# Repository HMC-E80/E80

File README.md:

# E80

This repository includes Arduino sketches (.ino) for the Teensy on the E80 motherboard.
The files for each lab are included in a separate folder.
The .ino files in each lab folder share the same name as the folder (e.g., `E80_Lab_01.ino` is in a folder named `E80_Lab_01.ino`).
This is a requirement for the Arduino IDE.

This respository also includes a [folder](./libraries/) of all the libraries you need for the various hardware peripherals on your motherboard (e.g., the GPS, and intertial measurement unit (IMU)).

The [MATLAB](./MATLAB/) folder contains the various MATLAB `.m` files which are used throughout the labs.

# How to Use this Repository

## Git Setup
You will need to configure Git on your machine.
Git is a distributed version control system.
This means you can download a local clone of a collection of source code files and easily track the changes that you make to your code.
While we won't be using all the features of git in E80, we will introduce you to the main features that will enable you to interact with the code base for your robot.

First, you need to install Git on your computer.
We recommend that for this class you use [Git Desktop](https://desktop.github.com) which provides a convenient GUI interface for interacting with the code.

1. Download and install the latest version of Git Desktop [here](https://desktop.github.com).
2. Navigate to the [E80 GitHub repository](https://github.com/HMC-E80/E80) and click `Code > Open with GitHub Desktop`. You will get a prompt to clone/download the repo, and GitHub Desktop will ask you where to save the files. Choose a location on your hard drive where you want to save the files (i.e., NOT in a folder that is synchronized in the cloud like a Google Drive File Stream folder). You should choose a location on your hard drive to minimize the chances of having any data corrupted.
   - NOTE: If for some reason clicking `Open with GitHub Desktop` is not working properly, simply copy the URL for the repository (e.g., `https://github.com/HMC-E80/E80`) and then manually clone the repository in GitHub Desktop using `File > Clone Repository`. Enter the copied URL into the "Respository URL" field.

## Arduino IDE Setup
Follow the instructions below to download and use this code within the Arduino IDE.
1. If you have not yet installed the Arduino IDE, install it from [here](https://www.arduino.cc/en/software). The version as of this writing is 2.0.3 but higher version numbers should also work fine.
2. Follow the instructions [here](https://www.pjrc.com/arduino-ide-2-0-0-teensy-support/) to configure support for the Teensy board within the Arduino IDE.
3. After downloading the code, open the Arduino IDE and go to __Arduino IDE > Settings__ if you are using a MAC and __file > preferences__ if you are using Windows. Change the Sketchbook location to point to the folder you downloaded from GitHub.

4. Now you if you click on the Sketchbook icon in the toolbar on the left side of the Arduino IDE you should see all the code for your E80 motherboard listed and available. Open up the `E80_Lab_01.ino` sketch and Verify it to check that it compiles and all the libraries are properly downloaded.

Congratulations, you are now set up and have the default E80 source code downloaded!
If you have any issues with these instructions, please reach out to one of the instructors.

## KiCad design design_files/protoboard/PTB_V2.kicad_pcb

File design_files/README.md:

# E80 Hardware Design Files

This directory contains the hardware design files for the E80 robot platform, including PCB schematics, layouts, and gerber files.

## Directory Structure

- **adapter_board/** - Design files for the Teensy 4.0 to 3.2 adapter board
  - KiCad project files and custom component libraries

- **motherboard/** - Design files for the main E80 Motherboard (MTB)
  - Schematics, PCB layouts, and documentation
  - Contains MTB_V3.0.2021 with complete KiCad project files

- **protoboard/** - Design files for the prototyping board (PTB)
  - Includes KiCad project files and gerber files for manufacturing

## Usage

These design files are provided for reference and can be viewed or modified using KiCad 5.0 or later. The gerber files in the PTB_V2_Gerbers directory can be sent directly to PCB manufacturers for reproduction.

## Documentation

Schematic PDFs are provided for the motherboard in the motherboard directory for easy reference without needing to open KiCad.

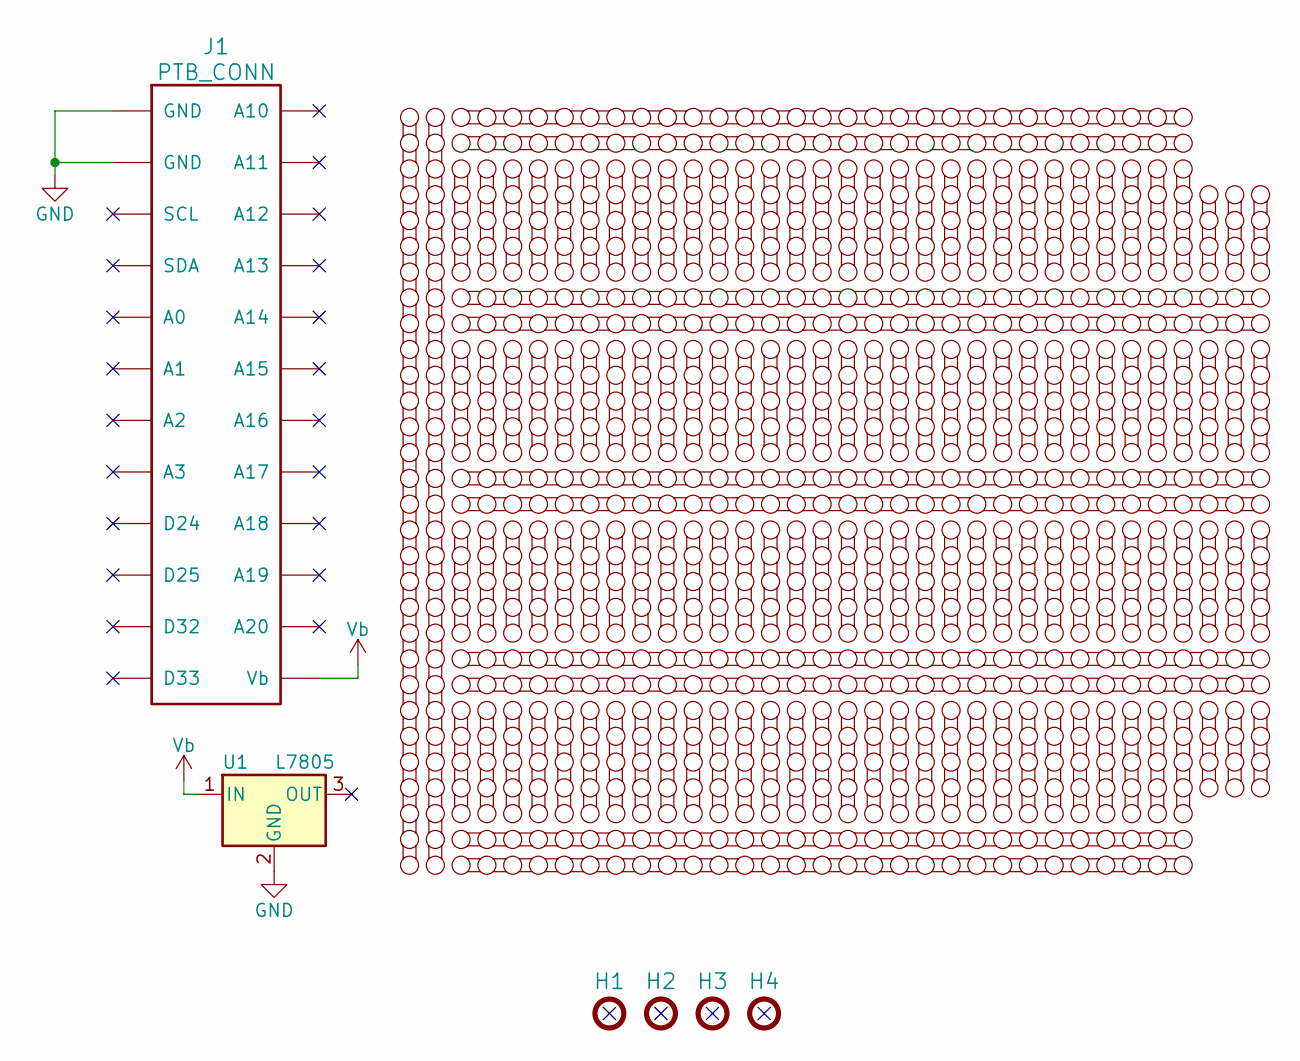
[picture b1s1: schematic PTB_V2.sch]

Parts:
H1, H2, H3, H4: MOUNTING_HOLE; Mounting_Hole
J1: PTB_CONN
U1: L7805; VREG
U2, U3: Row_30; Pad_30
U4, U5, U140, U141: Row_29; Pad_29
U6, U7, U8, U9, U10, U11, U12, U13, U14, U15, U16, U17, U18, U19, U20, U21, U22, U23, U24, U25, U26, U27, U28, U29, U30, U31, U32, U33, U34, U40, U41, U42, U43, U44, U45, U46, U47, U48, U49, U50, U51, U52, U53, U54, U55, U56, U57, U58, U59, U60, U61, U62, U63, U64, U65, U66, U67, U68, U69, U70, U71, U74, U75, U76, U77, U78, U79, U80, U81, U82, U83, U84, U85, U86, U87, U88, U89, U90, U91, U92, U93, U94, U95, U96, U97, U98, U99, U100, U101, U102, U103, U104, U105, U108, U109, U110, U111, U112, U113, U114, U115, U116, U117, U118, U119, U120, U121, U122, U123, U124, U125, U126, U127, U128, U129, U130, U131, U132, U133, U134, U135, U136: Row_5; Pad_5
U35, U36, U37, U137, U138, U139: Row_4; Pad_4
U38, U39, U72, U73, U106, U107: Row_32; Pad_32

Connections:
GND: J1.1 (GND), J1.2 (GND), U1.2 (GND)
Vb: J1.13 (Vb), U1.1 (IN)

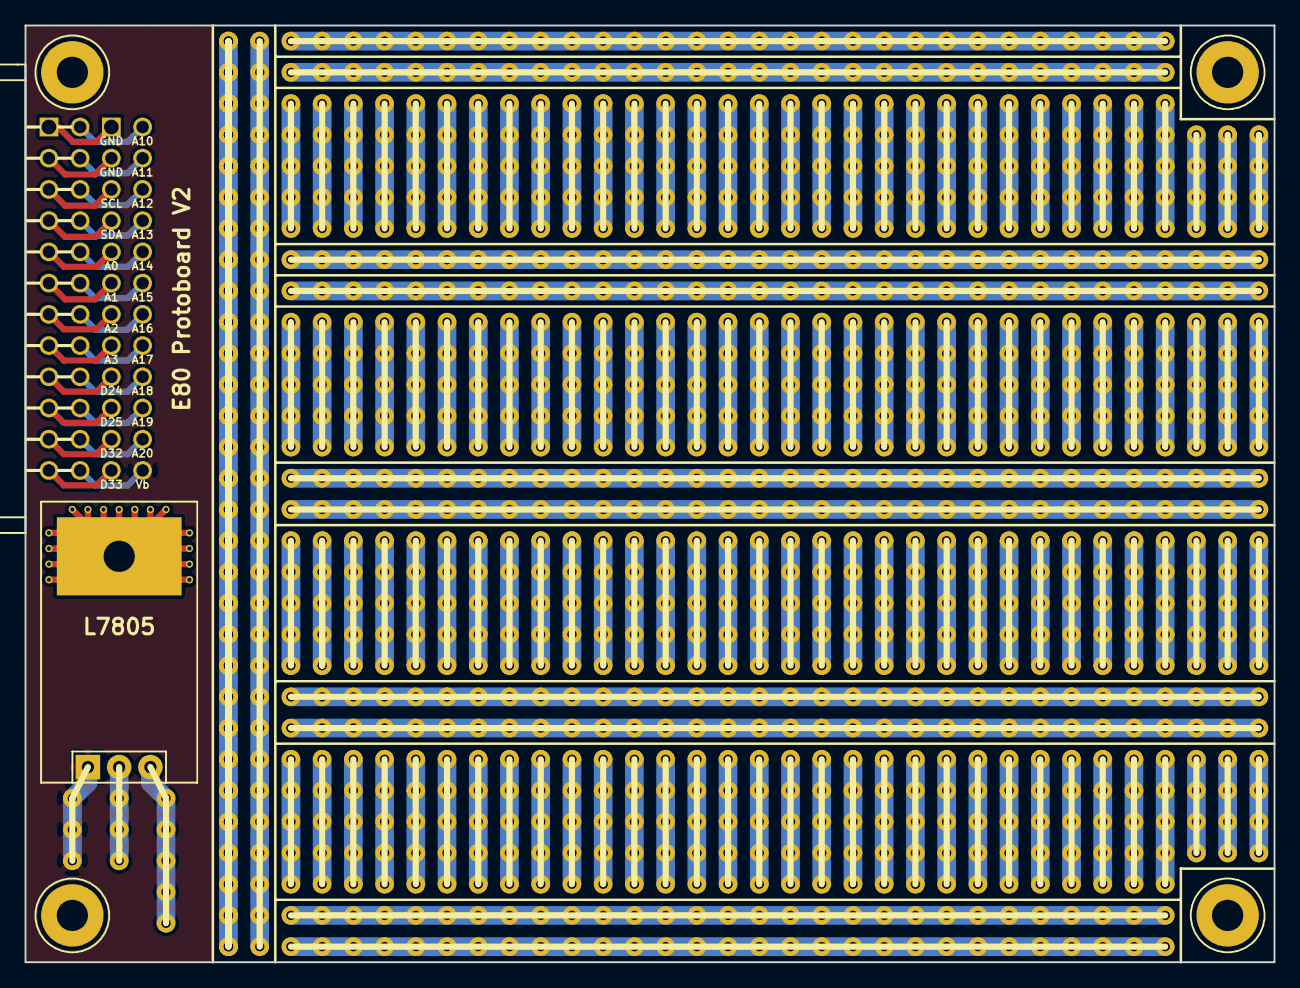
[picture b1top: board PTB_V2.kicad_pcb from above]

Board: 2 copper layers, 101.6 x 76.2 mm, 147 parts (0 on the bottom side), 2 nets.

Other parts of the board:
U3#2: Row_30; Pad_30

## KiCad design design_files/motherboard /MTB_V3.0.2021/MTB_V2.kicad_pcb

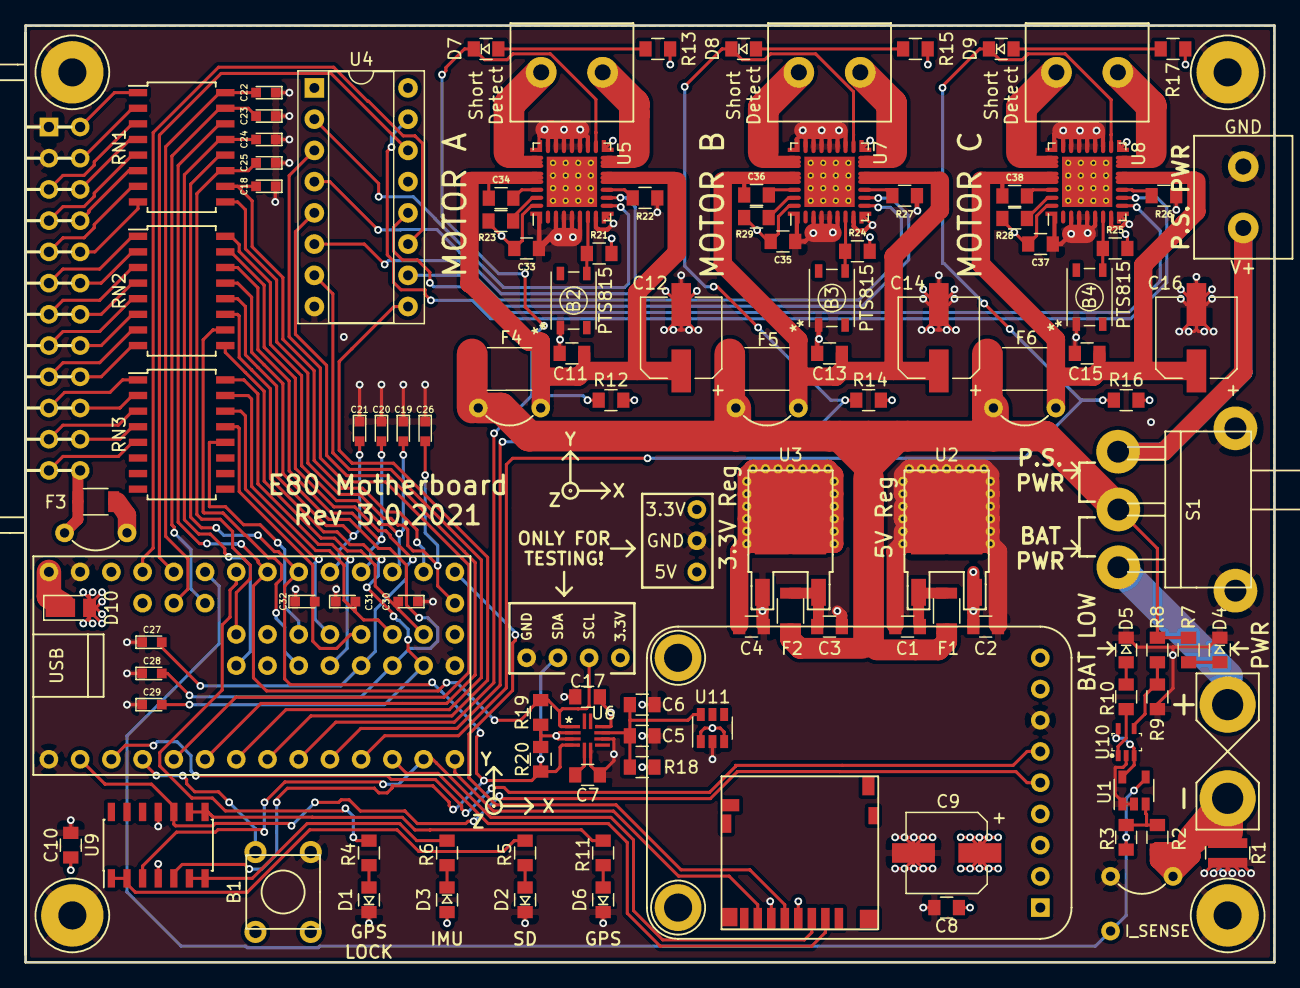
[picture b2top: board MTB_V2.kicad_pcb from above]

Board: 4 copper layers, 101.6 x 76.2 mm, 128 parts (0 on the bottom side), 115 nets.

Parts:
B1: Button; Push_Button
B2, B3, B4: PTS815; PTS815_SJK_250_SMTR_LFS
BT1: Battery; Battery_Connector
C1: 0.33uF; 0805
C2, C6, C7, C8, C10, C11, C13, C15, C17, C33, C34, C35, C36, C37, C38: 0.1uF; 0805
C3, C4, C5: 10uF; 0805
C9, C12, C14, C16: 100uF; CP_Elec_6.3x7.7
C18, C19, C20, C21, C22, C23, C24, C25, C26, C27, C28, C29, C30, C31, C32: 0.1uF; 0603
D1, D2, D3, D4, D5, D6, D7, D8, D9: LED; 0805_Diode
D10: D_Schottky; D_PowerDI-123
F1, F2, F3: 0.5A; 1206
F4, F5, F6: 1.5A; 1812
GPS1: GPS
H1, H2, H3, H4: MOUNTING_HOLE; Mounting_Hole
J1: PTB_CONN
J2: Motor A; 1x2_Screw_Terminal
J3: Motor B; 1x2_Screw_Terminal
J4: Motor C; 1x2_Screw_Terminal
J5: Scew_Terminal_1x2; 1x2_Screw_Terminal
JP1, JP2, JP3, JP4, JP5: Jumper
R1: 0.01; 0612
R2, R12, R14, R16, R19, R20, R21, R23, R24, R25, R28, R29: 10k; 0805
R3: 330k; 0805
R4, R5, R6, R10, R11, R13, R15, R17: 470; 0805
R7: 1.2k; 0805
R8: 30k; 0805
R9: 24k; 0805
R18: 68; 0805
R22, R26, R27: 200; 0805
RN1, RN2, RN3: R_Array_8; SOIC-16W_5.3x10.2mm_Pitch1.27mm
S1: Switch_SPDT; Battery_Switch
SD1: micro_SD; microSD
TP1, TP2, TP3, TP4, TP5, TP6, TP7, TP8: TEST_POINT; Test_Point
TSY1: Teensy3.2; Teensy
U1: MCP6V31; SOT-23-5
U2: L7805; TO-252-3_TabPin2
U3: LD1086; TO-252-3_TabPin2
U4: CD74HC4050; DIP-16_W7.62mm_Socket
U5, U7, U8: MC33HB2002ES; QFN-28_EP_6x6_Pitch0.65mm
U6: SON_03AGRTR_STM; LSM303AGRTR
U9: MCP6004; SOIC-14_3.9x8.7mm_Pitch1.27mm
U10: MCP6541; SC70
U11: LM3880; SOT-23-6

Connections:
1A: TSY1.5, U4.3
1Y: U4.2, U5.8
2A: TSY1.6, U4.5
2Y: U4.4, U5.9
3.3V: C4.1, C8.1, C9.1, C17.1, GPS1.1, R18.1, R19.2, R20.2, SD1.4, TP2.1, TP5.1, U3.2, U6.2, U6.3, U6.10, U11.1, U11.3
3A: TSY1.7, U4.7
3Y: U4.6, U7.8
4A: TSY1.8, U4.9
4Y: U4.10, U7.9
5A: TSY1.25, U4.11
5V: C2.1, C10.1, C33.2, C35.2, C37.2, D3.2, D10.2, R12.2, R13.2, R14.2, R15.2, R16.2, R17.2, R21.2, R23.1, R24.2, R25.2, R28.1, R29.1, TP3.1, U1.5, U2.3, U4.1, U5.28, U7.28, U8.28, U9.4, U10.3, U10.5
5Y: U4.12, U8.8
6A: TSY1.24, U4.14
6Y: U4.15, U8.9
A0: C18.2, RN1.10, TSY1.16
A1: C19.2, RN2.16, TSY1.17
A2: C20.2, RN2.14, TSY1.18
A3: C21.2, RN2.12, TSY1.19
A10: C22.2, RN1.16, TSY1.49
A11: C23.2, RN1.15, TSY1.48
A12: C24.2, RN1.13, TSY1.34
A13: C25.2, RN1.11, TSY1.47
A14: C26.2, RN1.9, TSY1.33
A15: C27.2, RN2.15, TSY1.38
A16: C28.2, RN2.13, TSY1.39
A17: C29.2, RN2.11, TSY1.40
A18: C30.2, RN2.9, TSY1.41
A19: C31.2, RN3.15, TSY1.42
A20: C32.2, RN3.13, TSY1.43
CS: SD1.2, TSY1.12
D24: RN2.10, TSY1.36
D25: RN3.16, TSY1.37
D32: RN3.14, TSY1.44
D33: RN3.12, TSY1.45
EF_A: D7.1, R12.1, TSY1.9, U5.15
EF_B: D8.1, R14.1, TSY1.10, U7.15
EF_C: D9.1, R16.1, TSY1.11, U8.15
GND: B1.1, B2.1, B3.1, B4.1, C1.2, C2.2, C3.2, C4.2, C5.2, C6.2, C7.2, C8.2, C9.2, C10.2, C11.2, C12.2, C13.2, C14.2, C15.2, C16.2, C17.2, C18.1, C19.1, C20.1, C21.1, C22.1, C23.1, C24.1, C25.1, C26.1, C27.1, C28.1, C29.1, C30.1, C31.1, C32.1, C33.1, C35.1, C37.1, D1.1, D2.1, D4.1, D5.1, D6.1, GPS1.7, H1.1, H2.1, H3.1, H4.1, J1.1, J1.2, J5.2, JP2.1, R1.1, R9.1, R22.1, R26.1, R27.1, S1.4, SD1.6, TP4.1, TP8.1, TSY1.1, TSY1.27, TSY1.31, U1.1, U1.2, U2.2, U3.1, U4.8, U5.2, U5.3, U5.4, U5.5, U5.7, U5.16, U5.17, U5.18, U5.19, U5.20, U5.21, U5.29, U5.30, U5.31, U5.32, U5.33, U6.6, U6.8, U7.2, U7.3, U7.4, U7.5, U7.7, U7.16, U7.17, U7.18, U7.19, U7.20, U7.21, U7.29, U7.30, U7.31, U7.32, U7.33, U8.2, U8.3, U8.4, U8.5, U8.7, U8.16, U8.17, U8.18, U8.19, U8.20, U8.21, U8.29, U8.30, U8.31, U8.32, U8.33, U9.11, U10.2, U11.2
I_SENSE: R3.2, TP1.1, TSY1.23, U1.4
MISO: SD1.7, TSY1.14
MOSI: SD1.3, TSY1.13, U9.3
unnamed: B1.2, TSY1.4
unnamed: B2.3, R21.1, U5.6
unnamed: B3.3, R24.1, U7.6
unnamed: B4.3, R25.1, U8.6
unnamed: BT1.1, S1.3
unnamed: BT1.2, JP2.2, R1.2, R2.1
unnamed: C1.1, F1.2, U2.1
unnamed: C3.1, F2.2, U3.3
unnamed: C7.1, U6.5
unnamed: C11.1, C12.1, C34.1, F4.2, JP1.2, U5.11, U5.12, U5.24, U5.25
unnamed: C13.1, C14.1, C36.1, F5.2, JP3.2, U7.11, U7.12, U7.24, U7.25
unnamed: C15.1, C16.1, C38.1, F6.2, JP4.2, U8.11, U8.12, U8.24, U8.25
unnamed: C34.2, U5.26
unnamed: C36.2, U7.26
unnamed: C38.2, U8.26
unnamed: D1.2, R4.1
unnamed: D2.2, R5.1
unnamed: D3.1, R6.1
unnamed: D4.2, R7.1
unnamed: D5.2, R10.1
unnamed: D6.2, R11.1
unnamed: D7.2, R13.1
unnamed: D8.2, R15.1
unnamed: D9.2, R17.1
unnamed: D10.1, TSY1.28
unnamed: F3.2, J1.13, JP5.1
unnamed: J1.3, RN1.3
unnamed: J1.4, RN1.5
unnamed: J1.5, RN1.7
unnamed: J1.6, RN2.1
unnamed: J1.7, RN2.3
unnamed: J1.8, RN2.5
unnamed: J1.9, RN2.7
unnamed: J1.10, RN3.1
unnamed: J1.11, RN3.3
unnamed: J1.12, RN3.5
unnamed: J1.14, RN3.4
unnamed: J1.15, RN3.2
unnamed: J1.16, RN2.8
unnamed: J1.17, RN2.6
unnamed: J1.18, RN2.4
unnamed: J1.19, RN2.2
unnamed: J1.20, RN1.8
unnamed: J1.21, RN1.6
unnamed: J1.22, RN1.4
unnamed: J1.23, RN1.2
unnamed: J1.24, RN1.1
unnamed: J2.1, U5.22, U5.23
unnamed: J2.2, U5.13, U5.14
unnamed: J3.1, U7.22, U7.23
unnamed: J3.2, U7.13, U7.14
unnamed: J4.1, U8.22, U8.23
unnamed: J4.2, U8.13, U8.14
unnamed: J5.1, S1.1
unnamed: R2.2, R3.1, U1.3
unnamed: R4.2, TSY1.22
unnamed: R5.2, U9.1, U9.2
unnamed: R6.2, U9.6, U9.7
unnamed: R8.1, R9.2, U10.4
unnamed: R10.2, U10.1
unnamed: R11.2, U9.8, U9.9
unnamed: R22.2, U5.10
unnamed: R23.2, U5.27
unnamed: R26.2, U8.10
unnamed: R27.2, U7.10
unnamed: R28.2, U8.27
unnamed: R29.2, U7.27
RX: GPS1.5, TSY1.2, U9.10
SCK: SD1.5, TSY1.15
SCL: R19.1, RN1.14, TP6.1, TSY1.21, U6.1
SDA: R20.1, RN1.12, TP7.1, TSY1.20, U6.4, U9.5
TX: GPS1.6, TSY1.3
Vb: F1.1, F2.1, F3.1, F4.1, F5.1, F6.1, JP1.1, JP3.1, JP4.1, JP5.2, R7.2, R8.2, S1.2
Vdd: C5.1, C6.1, R18.2, U6.9, U11.6

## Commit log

2023-01-23 Update logreader.m
    Fixed typo "you" data.
2023-01-24 Added Updated MotorDriver.h/cpp and Pinout
    Sorry gang
2023-01-24 Updated README formatting
2023-01-31 Updated matlab_logging.ino to turn off analogRead averaging
    After upgrading to the Teensy 4.0 from the 3.2 we noticed a change in the sampling frequency. The sampling rate by default seems to have 4-point averaging enabled, leading to a reduced sampling frequ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
    Calling `analogReadAveraging()` and manually setting the averaging to zero seems to resolve the issue.
2023-03-07 Changed plot axis units
    raw data from IMU is mGauss
    Removed Units from Calibrated Plot
2023-03-07 Added note about the IMU not using RHR
2023-04-03 ADCSampler: Update pinMap for Teensy 4.0
    Only 14 analog pins and pin numbers have changed
2023-04-04 Update SurfaceControl.cpp
    Added missing code in Surface Control for calculating the control effort for the motors using proportional control.
2023-04-05 Update XYStateEstimator.cpp
    Added calculation for x, y, and yaw in state estimator.
2023-04-18 Added KiCad files for MTB
    KiCad design files for v3.0 from the 2021 redesign along with PDFs of the schematic and board layout.
2023-04-20 Removed space after motherboard directory so that Windows is happy
2023-04-20 Changed file name for Windows compatibility
2023-05-02 Updated README to make naming general
    i.e., moving from E80-SP23 to E80
2023-05-02 Update .gitignore
    Add folders related to Quarto and website.
2024-01-09 added design files for tsy4.0 to 3.2 footprint adapter
2024-01-13 Squashed commit of the following:
    commit 36bdbc09f2571f2cda9d6bc650fdb4e2f4e75e4a
    Author: Josh Brake <joshbrake@users.noreply.github.com>
    Date: Fri Jan 12 13:32:22 2024 -0800
    Removed reference to E72
    commit 0d1cd06fd9c2b417d7891d901053c2ec7c6fedd3
    Author: Josh Brake <joshbrake@users.noreply.github.com>
2024-01-17 Changed ssh link to https link for cloning
2024-01-19 Added BurstADCSampler
2024-01-25 Squashed commit of the following:
    commit fa3ca03ef398e6306c82c8f771373e06a3e66b7b
    Author: Josh Brake <joshbrake@users.noreply.github.com>
    Date: Thu Jan 25 15:52:41 2024 -0800
    Updated Lab 1 page to link to writing assignment
    commit 46ee2d113efddf90a1995f49b687a478aaaf7760
    Author: Josh Brake <joshbrake@users.noreply.github.com>
2024-02-03 Merge pull request #5 from HMC-E80/josh-github-ci-setup
    Set up publish.yml file for CI publishing to gh-pages from main
2024-03-17 Matt jumpstart rewrite (#22)
    * Remove history page and put old designs under reference.
    * Tidy up figures, links and typos on references page
    * Clean up lab0 manual header
    * Consolidate board information on boards page, remove some other board refs.
    * Continuing WIP on project jump start and submission
    * Rename starter code. Minor edits
2024-03-17 Hot fix for Jump Start code: Patch a compile error in DepthControl
2024-03-22 Matt project build rewrite (#24)
    * Add some meteorological estimates to proposal page.
    * Quality of life improvements for jump start, including new figures.
    * History update w/ 2019 and 2023
    * Add side scan data to history
    * Add protoboard design files to repo. Will need to prune generated files (eg: gerbers) later.
    * Delete unused lab file.
2024-03-27 Squashed commit of the following:
    commit 6dc7d0d97dd0167760cb3333e43724efd9e2a891
    Author: xavi <xavi@xavishobbies.org>
    Date: Tue Mar 26 19:15:48 2024 -0700
    Renamed burst pins to NUM_BURST_PINS
    commit e6ff0ecc9a1b9360da7128e0a34916381f32c130
    Author: xavi <xavi@xavishobbies.org>
2024-05-03 Added design files, matlab scripts, and arduino sketchbook as submodules
2024-05-03 Removed design files, matlab scripts, and arduino sketchbook from top level
2025-03-28 Reorganize codebase structure and improve documentation
    - Move lab code to dedicated labs directory with standardized naming
    - Move example code to examples directory
    - Add README files with documentation for all directories
    - Update main README with new organization and improved setup instructions
2025-03-28 Added READMEs
2025-04-07 Patched waypoint bug
2025-04-09 Built site for gh-pages
2025-04-25 Fixed the ADC logging bug
    The header in the inf file included pins from the Teensy 3.2 that were no longer used in the Teensy 4.0. This caused an offset in the logged data which meant that the logreader was incorrectly readin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
2025-12-16 Corrected minor typos and increased clarity
2026-01-05 Removed web/ and .github/workflows/publish.yml
    Moved to a seperate repo. I also turned off the github action to build
    and deploy pages. It used to point to https://hmc-e80.github.io/E80/.
    The new one points at https://hmc-e80.github.io/.

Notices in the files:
parts and their libraries:
Copyright 2021 Accelerated Designs. All rights reserved.
